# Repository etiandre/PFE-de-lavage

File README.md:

View this project on [CADLAB.io](https://cadlab.io/project/2356). 

# PFE-de-lavage

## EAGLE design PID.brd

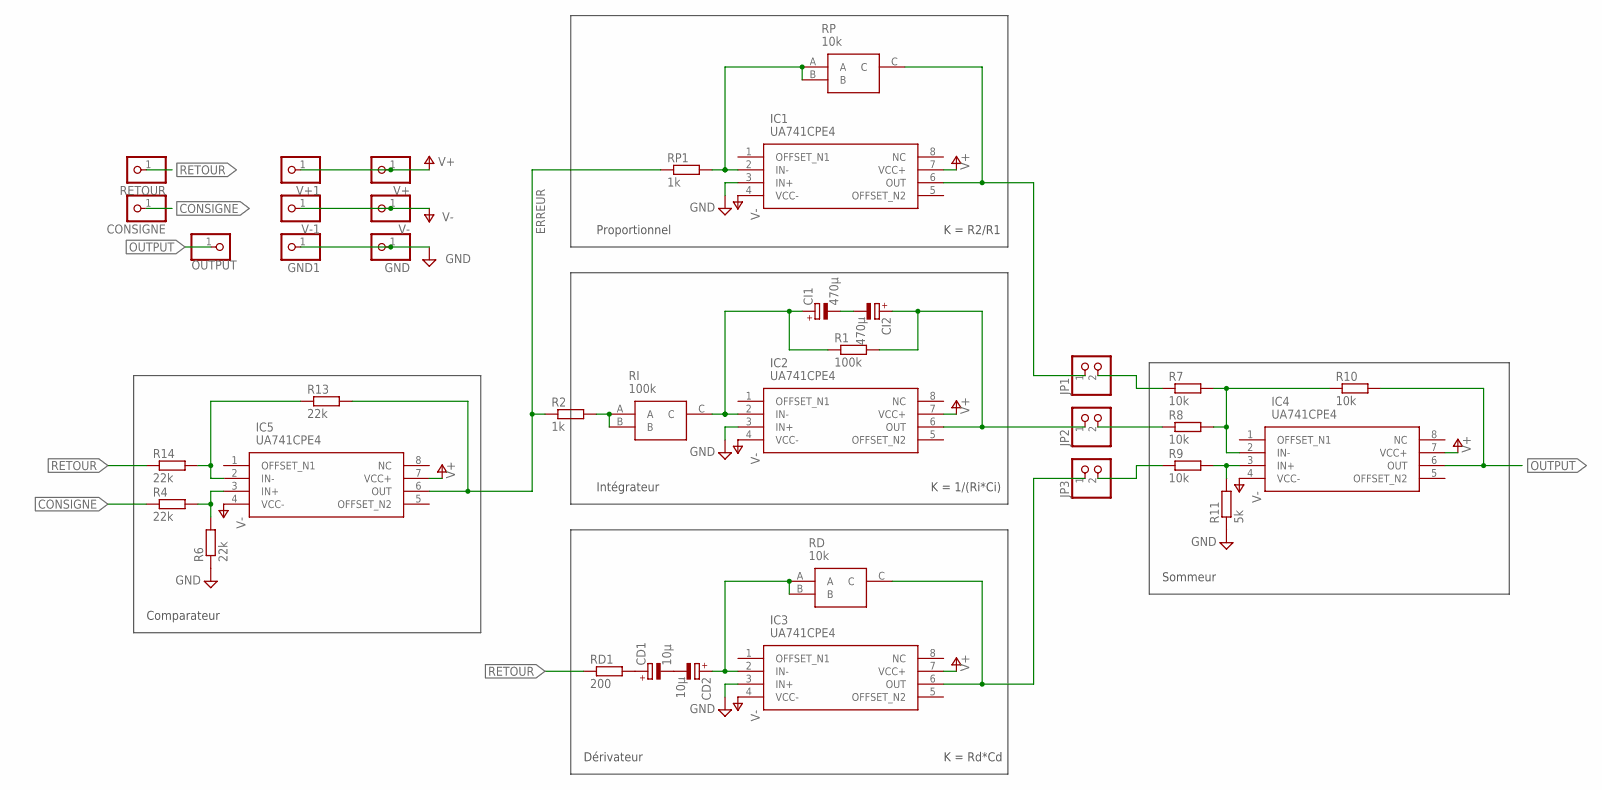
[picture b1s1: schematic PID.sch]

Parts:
CD1, CD2: 10µ; E2,5-6
CI1, CI2: 470µ; E2,5-6
CONSIGNE: PINHD-1X1; 1X01
GND, GND1: PINHD-1X1; 1X01
IC1, IC2, IC3, IC4, IC5: UA741CPE4; DIP794W53P254L959H508Q8N
JP1, JP2, JP3: PINHD-1X2; 1X02
OUTPUT: PINHD-1X1; 1X01
R1: 100k; 0204/7
R2: 1k; 0204/7
R4, R6, R13, R14: 22k; 0204/7
R7, R8, R9, R10: 10k; 0204/7
R11: 5k; 0204/7
RD: 10k; T7YA
RD1: 200; 0204/7
RETOUR: PINHD-1X1; 1X01
RI: 100k; T7YA
RP: 10k; T7YA
RP1: 1k; 0204/7
V+, V+1: PINHD-1X1; 1X01
V-, V-1: PINHD-1X1; 1X01

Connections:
CONSIGNE: CONSIGNE.1, R4.1
ERREUR: IC5.6 (OUT), R2.1, R13.2, RP1.1
GND: GND.1, GND1.1, IC1.3 (IN+), IC2.3 (IN+), IC3.3 (IN+), R6.1, R11.1
unnamed: IC1.6 (OUT), JP1.1, RP.C
unnamed: IC1.2 (IN-), RP.A, RP.B, RP1.2
unnamed: CI2.+, IC2.6 (OUT), JP2.1, R1.2
unnamed: CI1.+, IC2.2 (IN-), R1.1, RI.C
unnamed: IC4.2 (IN-), R7.2, R8.2, R10.1
unnamed: CI1.-, CI2.-
unnamed: IC5.2 (IN-), R13.1, R14.2
unnamed: IC3.6 (OUT), JP3.1, RD.C
unnamed: CD2.+, IC3.2 (IN-), RD.A, RD.B
unnamed: JP1.2, R7.1
unnamed: IC5.3 (IN+), R4.2, R6.2
unnamed: CD1.-, CD2.-
unnamed: R2.2, RI.A, RI.B
unnamed: JP2.2, R8.1
unnamed: CD1.+, RD1.2
unnamed: IC4.3 (IN+), R9.2, R11.2
unnamed: JP3.2, R9.1
OUTPUT: IC4.6 (OUT), OUTPUT.1, R10.2
RETOUR: R14.1, RD1.1, RETOUR.1
V+: IC1.7 (VCC+), IC2.7 (VCC+), IC3.7 (VCC+), IC4.7 (VCC+), IC5.7 (VCC+), V+.1, V+1.1
V-: IC1.4 (VCC-), IC2.4 (VCC-), IC3.4 (VCC-), IC4.4 (VCC-), IC5.4 (VCC-), V-.1, V-1.1

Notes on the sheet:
Proportionnel
Intégrateur
Dérivateur
Comparateur
Sommeur
K = 1/(Ri*Ci)
K = R2/R1
K = Rd*Cd

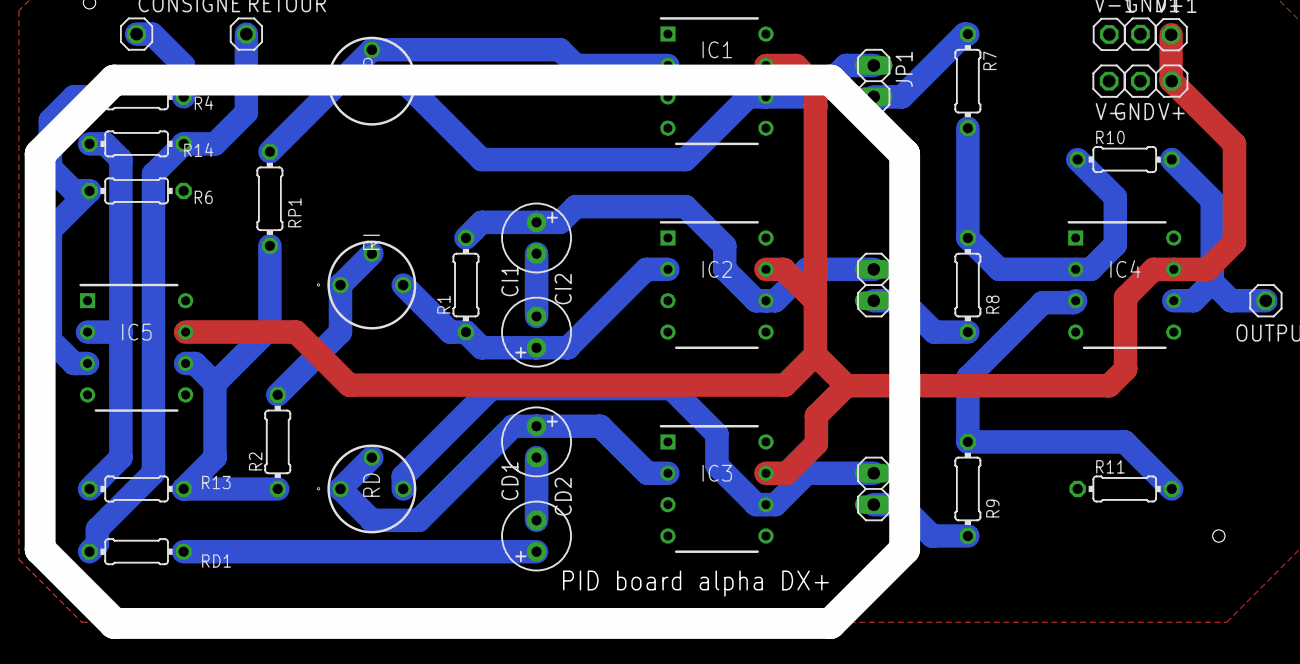
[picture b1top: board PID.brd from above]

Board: 2 copper layers, 37 parts (0 on the bottom side), 24 nets.

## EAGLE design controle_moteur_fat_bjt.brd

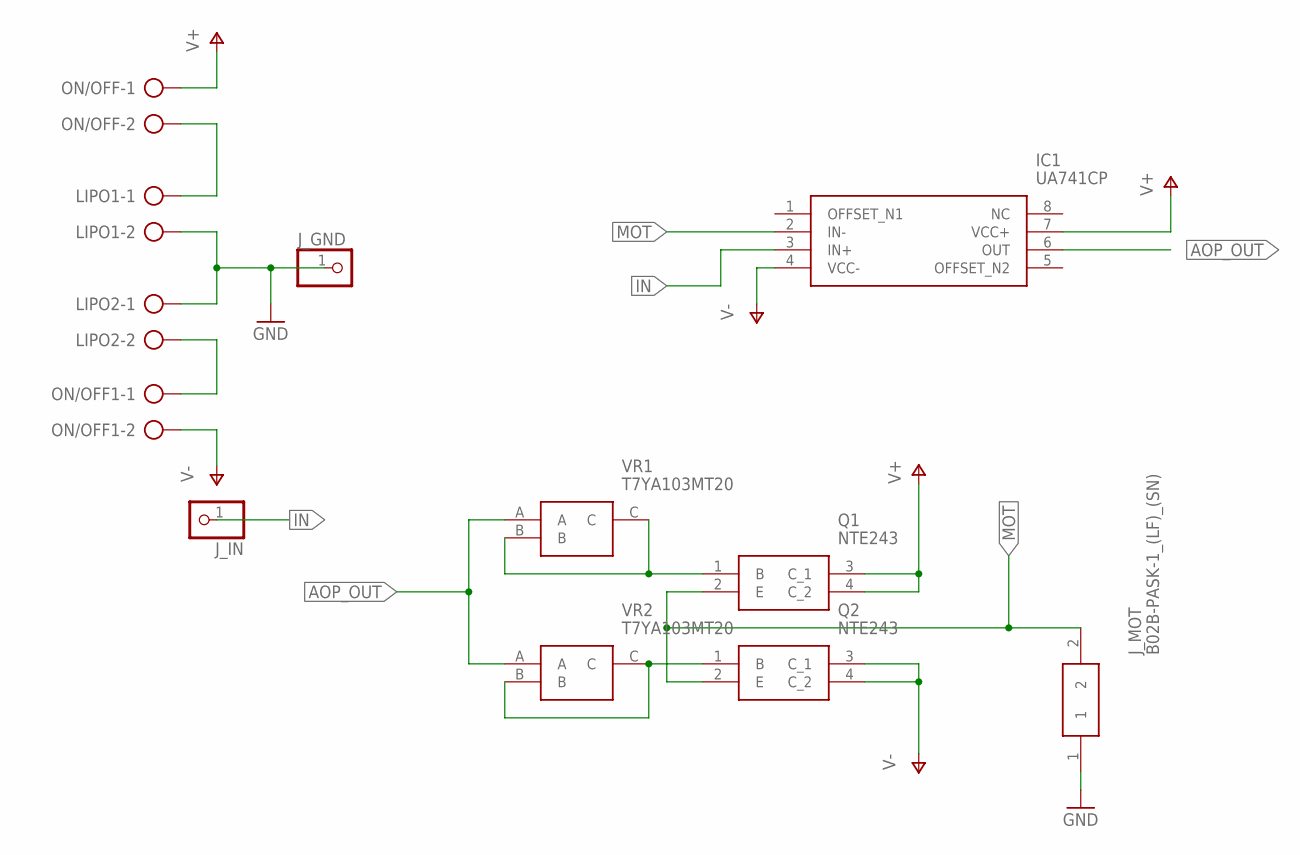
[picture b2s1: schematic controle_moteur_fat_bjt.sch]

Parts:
IC1: UA741CP; DIP794W53P254L959H508Q8N
J_GND: PINHD-1X1; 1X01
J_IN: PINHD-1X1; 1X01
J_MOT: B02B-PASK-1_(LF)_(SN); B02BPASK1LFSN
LIPO1, LIPO2: AK500/2
ON/OFF, ON/OFF1: AK500/2
Q1, Q2: NTE243
VR1, VR2: T7YA103MT20; T7YA

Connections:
AOP_OUT: IC1.6 (OUT), VR1.A, VR2.A
GND: J_GND.1, J_MOT.1, LIPO1.2, LIPO2.1
IN: IC1.3 (IN+), J_IN.1
MOT: IC1.2 (IN-), J_MOT.2, Q1.2 (E), Q2.2 (E)
unnamed: LIPO1.1, ON/OFF.2
unnamed: Q1.1 (B), VR1.B, VR1.C
unnamed: Q2.1 (B), VR2.B, VR2.C
V+: IC1.7 (VCC+), ON/OFF.1, Q1.3 (C_1), Q1.4 (C_2)
V+1: LIPO2.2, ON/OFF1.1
V-: IC1.4 (VCC-), ON/OFF1.2, Q2.3 (C_1), Q2.4 (C_2)

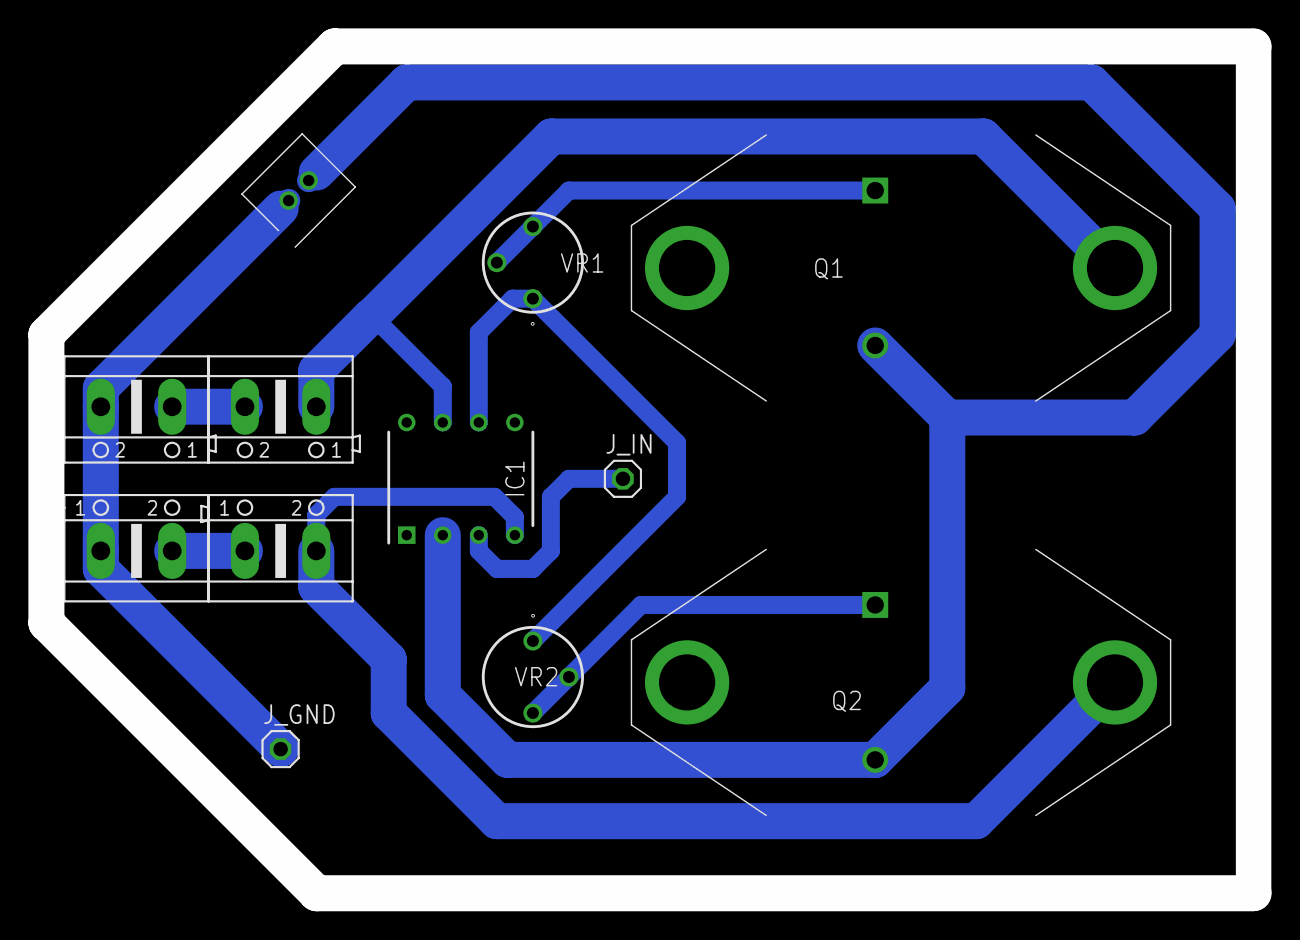
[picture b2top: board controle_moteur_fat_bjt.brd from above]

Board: 2 copper layers, 85.1 x 59.7 mm, 12 parts (0 on the bottom side), 10 nets.

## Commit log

2019-12-11 Backlink to CADLAB.io has been added.
2019-12-12 couocu
2019-12-24 Le routage de lavage, tous les signaux sur le bottom, le plan de masse sur le bottom, plan de V- sur le top et routage du V+ sur le top
2020-01-06 added the pdfs
